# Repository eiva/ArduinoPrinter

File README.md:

ArduinoPrinter
==============

Try to make termoprinter from АМС-100К.
It is now finaly works.

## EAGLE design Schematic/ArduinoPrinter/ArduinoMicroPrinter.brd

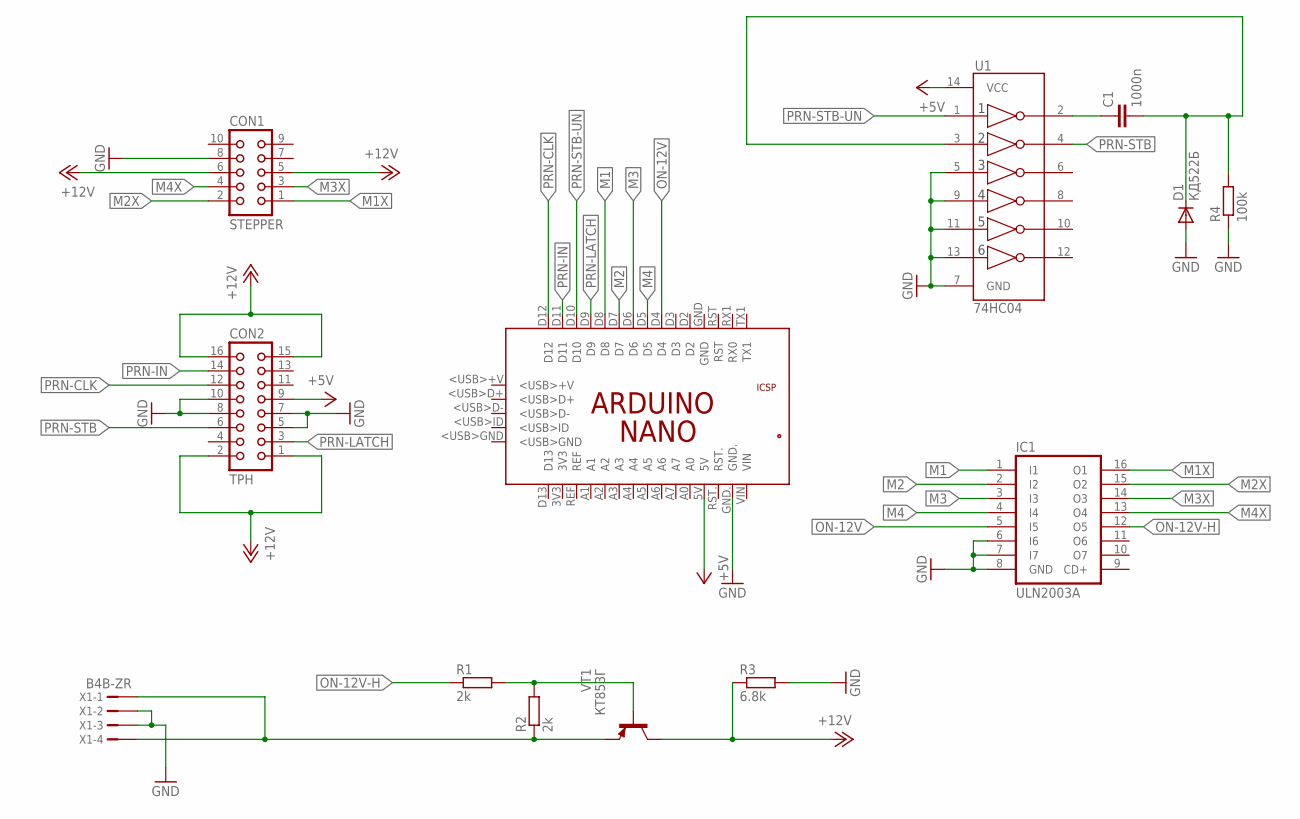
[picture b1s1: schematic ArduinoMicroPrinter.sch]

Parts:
C1: 1000n; C075-032X103
CON1: STEPPER; CON10; MPN 0-281273-1
CON2: TPH; CON16; MPN 1-1634688-0
D1: КД522Б; DO35-10
IC1: ULN2003A; DIL16
PCB1: ARDUINO_NANO; MPN A000005
R1, R2: 2k; 0207/12
R3: 6.8k; 0207/12
R4: 100k; 0309/12
U1: 74HC04; DIL14
VT1: КТ853Г; TO220
X1: B4B-ZR

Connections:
+5V: CON2.9, PCB1.5V, U1.14 (VCC)
+12V: CON1.5, CON1.6, CON2.1, CON2.2, CON2.15, CON2.16, R3.1, VT1.2 (C)
GND: CON1.8, CON2.5, CON2.7, CON2.8, CON2.10, D1.A, IC1.6 (I6), IC1.7 (I7), IC1.8 (GND), PCB1.GND., R3.2, R4.1, U1.5 (3A), U1.7 (GND), U1.9 (4A), U1.11 (5A), U1.13 (6A), X1.2, X1.3
M1: IC1.1 (I1), PCB1.D8
M1X: CON1.1, IC1.16 (O1)
M2: IC1.2 (I2), PCB1.D7
M2X: CON1.2, IC1.15 (O2)
M3: IC1.3 (I3), PCB1.D6
M3X: CON1.3, IC1.14 (O3)
M4: IC1.4 (I4), PCB1.D5
M4X: CON1.4, IC1.13 (O4)
unnamed: C1.1, U1.2 (1Y)
unnamed: C1.2, D1.C, R4.2, U1.3 (2A)
unnamed: R1.2, R2.2, VT1.1 (B)
unnamed: R2.1, VT1.3 (E), X1.1, X1.4
ON-12V: IC1.5 (I5), PCB1.D4
ON-12V-H: IC1.12 (O5), R1.1
PRN-CLK: CON2.12, PCB1.D12
PRN-IN: CON2.14, PCB1.D11
PRN-LATCH: CON2.3, PCB1.D9
PRN-STB: CON2.6, U1.4 (2Y)
PRN-STB-UN: PCB1.D10, U1.1 (1A)

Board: 2 copper layers, 13 parts (0 on the bottom side), 22 nets, no tracks yet.

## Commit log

2014-02-08 Initial commit
    Repo settings
2014-02-08 Printer Test Application
    Migrated Printer test application.
2014-02-08 Arduino sketch project for TPH controlling
    Migrated.
    Supports paper feeder control.
    Supports TPH control in mitmask raw mode
2014-02-08 Schematic for Printer PCB based on arduino nano
2014-02-08 Added 12V power switch
2014-02-09 Git makes strange thingth: It commit me from different account.
2014-02-09 Supports of a text printing. There one problem: lack of a good font and font experience.
2014-02-11 Added PCB layout not routed yet (I'm still not learn it).
2014-02-12 Added customized PCB with ATMega and FTDL
2014-04-10 Плата для Lcd.sch Описание для ардуино.
2014-05-10 Адаптация
